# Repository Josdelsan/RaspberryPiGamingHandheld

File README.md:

# Raspberry Pi Gaming Handheld

This repository contains all the information required in order to build a Raspberry Pi Zero (w/w 2) handheld gaming device. This project was done for educational purposes and it is not intended to be sold or distributed. The guides provided covers one or multiple solutions for each part of the device (Display, Power, Audio, Controls, etc.), the user is free to choose the one that fits their needs better. If you have any issues or you want to showcase your build, feel free to open an issue.

This project was especially designed for fitting a Raspberry Pi Zero inside a GameBoy Advance shell. The GameBoy Advance/GameBoy Color are great options for this project because they are cheap and easy to find. You can adapt the project to fit any other form factor you want.

*GBA based Raspberry Pi Zero 2 W handheld front view*

## Disclaimer

This project requires soldering skills and comprehensive knowledge abour RPI software and hardware. It is not recommended for beginners. Even if the parts cost are low, it may be more expensive than just buying an emulator handheld device like the [Miyoo Mini Plus](https://www.miyoogame.com/product/miyoo-mini-plus-retro-handheld-game-console/) or the [Anbernic RG35XXSP](https://anbernic.com/products/rg35xxsp).

When emulating games, please make sure you own the original copy of the game. This project does not provide any ROMs or information on how to obtain them. All the trademarks and copyrights are property of their respective owners.

## Photos

*GBA based Raspberry Pi Zero 2 W handheld top view*

*GBA based Raspberry Pi Zero 2 W handheld removed back shell*

*GBA based Raspberry Pi Zero 2 W handheld disassembled*

*First iteration of GBA based Raspberry Pi Zero W handheld gaming deviced without shell*

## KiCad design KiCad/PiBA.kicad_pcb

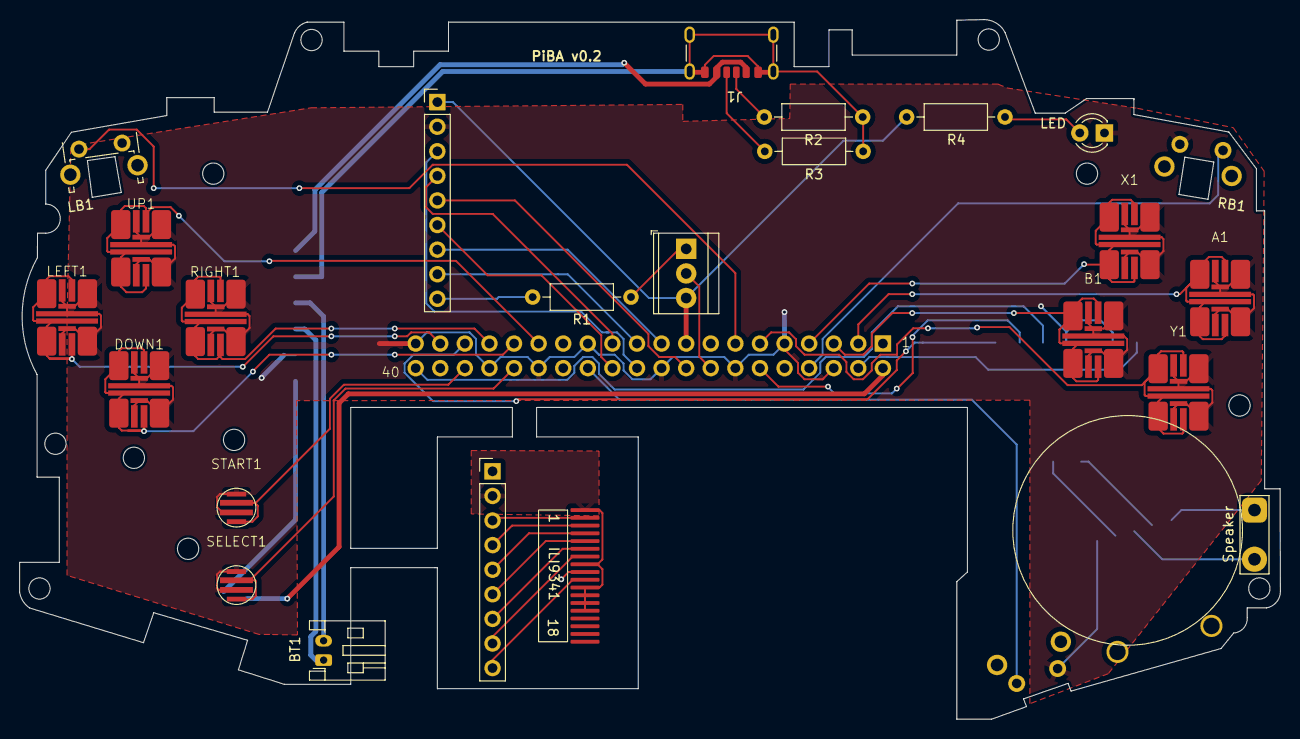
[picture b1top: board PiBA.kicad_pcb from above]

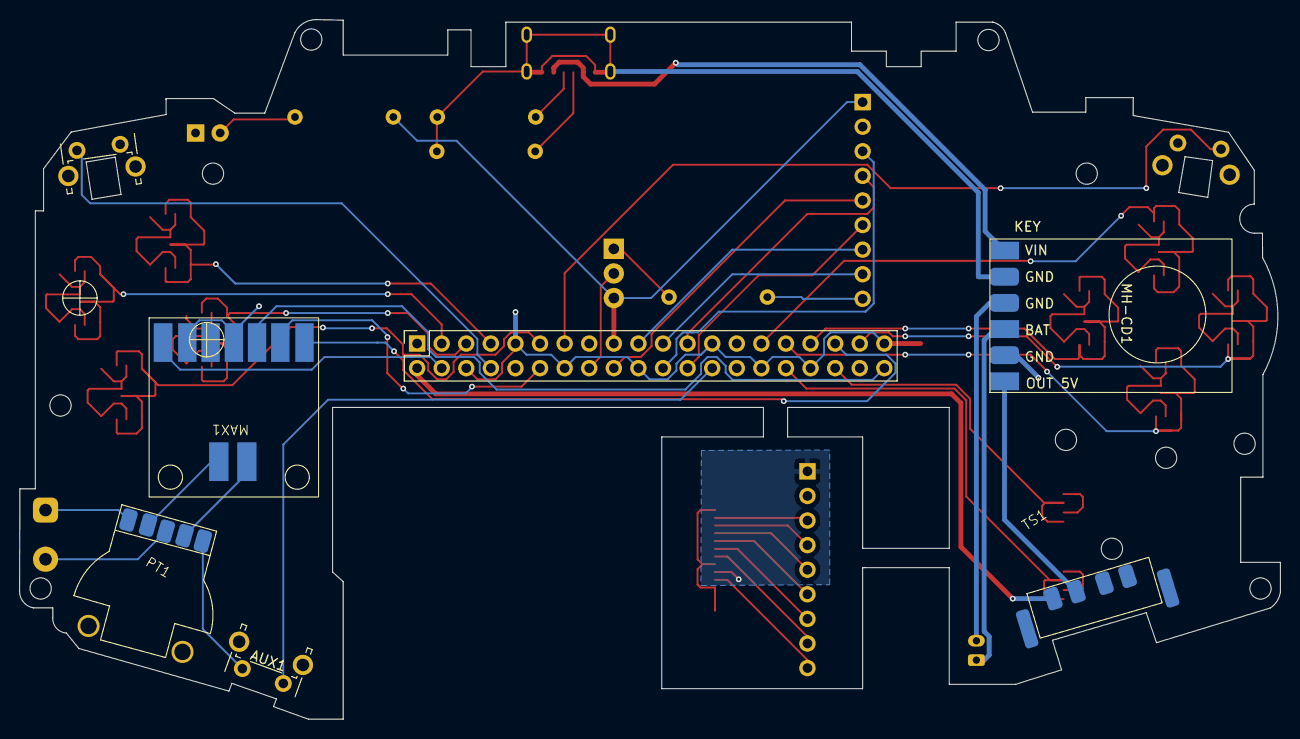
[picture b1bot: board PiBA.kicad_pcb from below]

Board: 2 copper layers, 130.2 x 72.3 mm, 30 parts (7 on the bottom side), 50 nets.

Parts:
A1: A; gba_button_switch_pad
AUX1: RB; SW_Tactile_SPST_Angled_PTS645Vx39-2LFS
B1: B; gba_button_switch_pad
BT1: Battery_Cell; JST_PH_S2B-PH-K_1x02_P2.00mm_Horizontal
D1: LED; LED_D3.0mm
DOWN1: DOWN; gba_button_switch_pad
ILI1: ILI9341 solder pad
ILI9341Extension1, ILI9341Extension2: PinHeader_1x09_P2.54mm_Vertical
J1: USB_C_Receptacle_PowerOnly_6P; USB_C_Receptacle_GCT_USB4125-xx-x_6P_TopMnt_Horizontal
J2: Conn_01x03; TerminalBlock_TE_282834-3_1x03_P2.54mm_Horizontal
LB1: LB; SW_Tactile_SPST_Angled_PTS645Vx39-2LFS
LEFT1: LEFT; gba_button_switch_pad
LS1: Speaker; TestPoint_2Pads_Pitch5.08mm_Drill1.3mm
MAX1: MAX98357
MH-CD1: MH-CD42
PT1: Pot b103
R1: 10R; R_Axial_DIN0207_L6.3mm_D2.5mm_P10.16mm_Horizontal
R2, R3: 5k1; R_Axial_DIN0207_L6.3mm_D2.5mm_P10.16mm_Horizontal
R4: 150R; R_Axial_DIN0207_L6.3mm_D2.5mm_P10.16mm_Horizontal
RB1: RB; SW_Tactile_SPST_Angled_PTS645Vx39-2LFS
RIGHT1: RIGHT; gba_button_switch_pad
RaspberryPiZero2W1: RPIZero
SELECT1: SELECT; gba_button_stsl
START1: START; gba_button_stsl
TS1: Toggle switch
UP1: UP; gba_button_switch_pad
X1: X; gba_button_switch_pad
Y1: Y; gba_button_switch_pad

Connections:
+3V3: ILI9341Extension2.1 (VCC), J2.3, R4.1, RaspberryPiZero2W1.17 (3V3)
+5V: MAX1.1 (VIN), RaspberryPiZero2W1.4 (5V)
BAT GND: BT1.2 (-), MH-CD1.4 (GND)
GND: A1.2, AUX1.2, B1.2, D1.1, DOWN1.2, ILI9341Extension2.2 (GND), LB1.2, LEFT1.2, MAX1.2 (GND), MAX1.4 (GAIN), MH-CD1.2 (GND), PT1.1 (GND), RB1.2, RIGHT1.2, RaspberryPiZero2W1.6 (GND), RaspberryPiZero2W1.9 (GND), RaspberryPiZero2W1.14 (GND), RaspberryPiZero2W1.20 (GND), RaspberryPiZero2W1.25 (GND), RaspberryPiZero2W1.30 (GND), RaspberryPiZero2W1.34 (GND), RaspberryPiZero2W1.39 (GND), SELECT1.2, START1.2, UP1.2, X1.2, Y1.2
GPIO2: A1.1, RaspberryPiZero2W1.3 (GPIO2/SDA1)
GPIO3: B1.1, RaspberryPiZero2W1.5 (GPIO3/SCL1)
GPIO4: RaspberryPiZero2W1.7 (GPIO4/GPIO_GCLK), X1.1
GPIO5: RaspberryPiZero2W1.29 (GPIO5), UP1.1
GPIO6: DOWN1.1, RaspberryPiZero2W1.31 (GPIO6)
GPIO7: AUX1.1, RaspberryPiZero2W1.26 (SPI_CE1_N/GPIO7)
GPIO12: RaspberryPiZero2W1.32 (GPIO12), SELECT1.1
GPIO13: RIGHT1.1, RaspberryPiZero2W1.33 (GPIO13)
GPIO14: RB1.1, RaspberryPiZero2W1.8 (TXD0/GPIO14)
GPIO16: RaspberryPiZero2W1.36 (GPIO16), START1.1
GPIO17: RaspberryPiZero2W1.11 (GPIO17/GPIO_GEN0), Y1.1
GPIO18: MAX1.6 (BCLK), RaspberryPiZero2W1.12 (GPIO_GEN1/GPIO18)
GPIO19: MAX1.7 (LRC), RaspberryPiZero2W1.35 (GPIO19)
GPIO21: MAX1.5 (DIN), RaspberryPiZero2W1.40 (GPIO21)
GPIO26: LEFT1.1, RaspberryPiZero2W1.37 (GPIO26)
GPIO27: LB1.1, RaspberryPiZero2W1.13 (GPIO27/GPIO_GEN2)
unnamed: BT1.1 (+), MH-CD1.3 (BAT_3V7)
unnamed: D1.2, R4.2
unnamed: ILI1.9 (3V3), ILI9341Extension1.1 (VCC)
unnamed: ILI1.3 (CLK), ILI9341Extension1.4 (CLK)
unnamed: ILI1.5 (CS), ILI9341Extension1.6 (CS)
unnamed: ILI1.4 (DC), ILI9341Extension1.5 (DC)
unnamed: ILI1.10 (LEDA), ILI9341Extension1.9 (LED)
unnamed: ILI1.1 (GND), ILI1.8 (GND), ILI1.11 (LEDK1), ILI1.12 (LEDK2), ILI1.13 (LEDK3), ILI1.14 (LEDK4), ILI9341Extension1.2 (GND)
unnamed: ILI1.2 (RESET), ILI9341Extension1.3 (RESET)
unnamed: ILI1.6 (SDI/SDA), ILI9341Extension1.7 (SDI)
unnamed: ILI1.7 (SDO), ILI9341Extension1.8 (SDO)
unnamed: ILI9341Extension2.9 (LED), R1.1
unnamed: J1.A5 (CC1), R2.2
unnamed: J1.B5 (CC2), R3.2
unnamed: J2.1, R1.2
unnamed: MAX1.8 (S1), PT1.2 (Ch1_IN)
unnamed: MAX1.9 (S2), PT1.4 (Ch2_IN)
unnamed: J1.A9 (VBUS), J1.B9 (VBUS), MH-CD1.6 (VIN_5V)
unnamed: LS1.1, PT1.5 (Ch1_OUT)
unnamed: LS1.2, PT1.3 (Ch2_OUT)
PIN GND: J1.A12 (GND), J1.B12 (GND), J1.S1 (SHIELD), MH-CD1.5 (GND), R2.1, R3.1
POWER: MH-CD1.1 (OUT_5V), TS1.2
POWERIN: RaspberryPiZero2W1.2 (5V), TS1.1
clk: ILI9341Extension2.4 (CLK), RaspberryPiZero2W1.23 (GPIO11/SPI_SCLK)
cs: ILI9341Extension2.6 (CS), RaspberryPiZero2W1.24 (SPI_CE0_N/GPIO8)
dc: ILI9341Extension2.5 (DC), RaspberryPiZero2W1.18 (GPIO_GEN5/GPIO24)
led: J2.2, RaspberryPiZero2W1.16 (GPIO_GEN4/GPIO23)
reset: ILI9341Extension2.3 (RESET), RaspberryPiZero2W1.22 (GPIO_GEN6/GPIO25)
sdi: ILI9341Extension2.7 (SDI), RaspberryPiZero2W1.19 (GPIO10/SPI_MOSI)
sdo: ILI9341Extension2.8 (SDO), RaspberryPiZero2W1.21 (GPIO9/SPI_MISO)
